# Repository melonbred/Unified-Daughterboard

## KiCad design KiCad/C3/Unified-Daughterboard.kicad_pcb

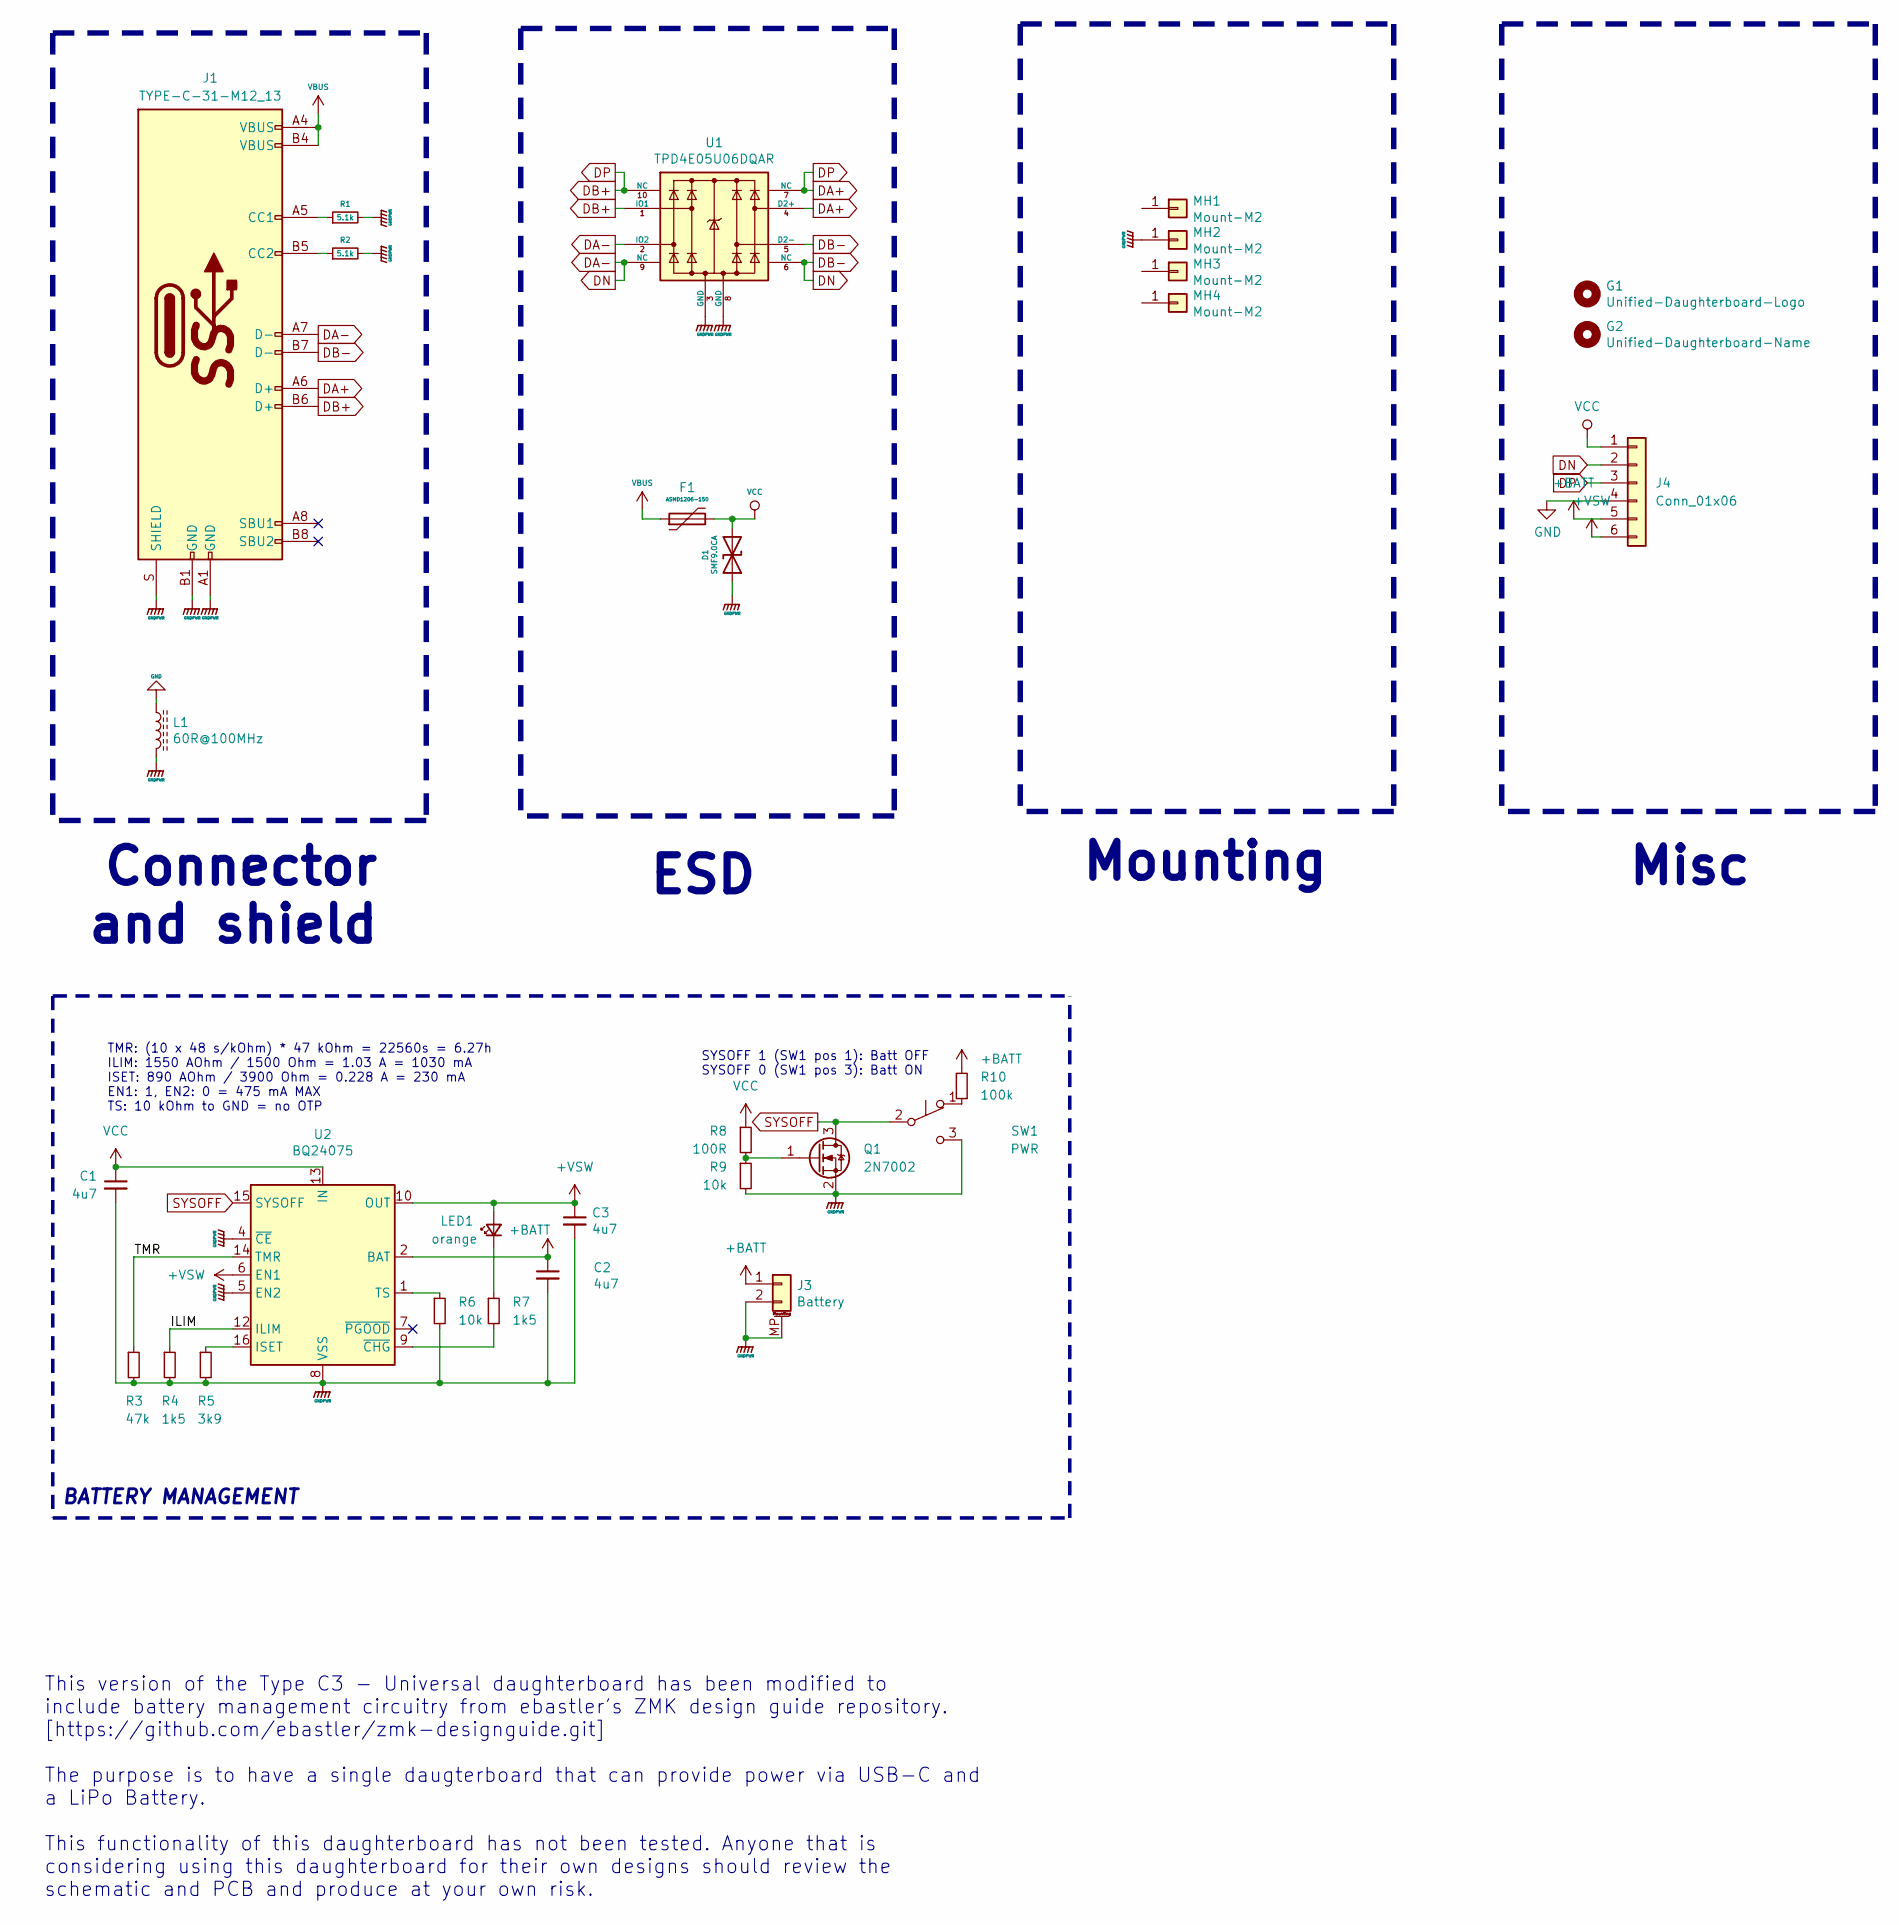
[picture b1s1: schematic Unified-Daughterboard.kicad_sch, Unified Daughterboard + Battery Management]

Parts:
C1, C2, C3: 4u7; C_0402_1005Metric
D1: SMF9.0CA; D_SOD-123_Bidirectional; Manufacturer Part No SMF9.0CA; LCSC Part No C123799
F1: ASMD1206-150; Fuse_1206_3216Metric; Manufacturer Part No ASMD1206-150; LCSC Part No C135342
G1: Unified-Daughterboard-Logo; Unified-Daughterboard-Logo.pretty
G2: Unified-Daughterboard-Name; Unified-Daughterboard-Name.pretty
J1: TYPE-C-31-M12_13; TYPE-C-31-M-12; Manufacturer Part No TYPE-C-31-M-12; LCSC Part No C165948
J3: Battery; JST_SH_SM02B-SRSS-TB_1x02-1MP_P1.00mm_Horizontal; LCSC C505023
J4: Conn_01x06; Molex_Pico-EZmate_78171-5006_1x06-1MP_P1.20mm_Vertical
L1: 60R@100MHz; L_1206_3216Metric; Manufacturer Part No MLB3216-600P4A(f); LCSC Part No C33600
LED1: orange; LED_0402_1005Metric; LCSC C917185
MH1, MH2, MH3, MH4: Mount-M2; Generic-Mounthole
Q1: 2N7002; SOT-23
R1, R2: 5.1k; R_0603
R3: 47k; R_0402_1005Metric
R4, R7: 1k5; R_0402_1005Metric
R5: 3k9; R_0402_1005Metric
R6, R9: 10k; R_0402_1005Metric
R8: 100R; R_0402_1005Metric
R10: 100k; R_0402_1005Metric
SW1: PWR; SW_MSK12C02-HB
U1: TPD4E05U06DQAR; USON-10_2.5x1.0mm_P0.5mm; Manufacturer Part No TPD4E05U06DQAR; LCSC Part No C138714
U2: BQ24075; VQFN-16-1EP_3x3mm_P0.5mm_EP1.6x1.6mm; LCSC C15464

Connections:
+BATT: C2.1, J3.1, J4.5, R10.2, U2.2 (BAT), U2.3 (BAT)
+VSW: C3.1, J4.6, LED1.2 (A), U2.6 (EN1), U2.10 (OUT), U2.11 (OUT)
/ILIM: R4.1, U2.12 (ILIM)
/TMR: R3.1, U2.14 (TMR)
DA+: J1.A6 (D+), J1.B6 (D+), J4.3, U1.1 (IO1), U1.4 (D2+), U1.7 (NC), U1.10 (NC)
DA-: J1.A7 (D-), J1.B7 (D-), J4.2, U1.2 (IO2), U1.5 (D2-), U1.6 (NC), U1.9 (NC)
GND: J4.4, L1.1
GNDPWR: C1.2, C2.2, C3.2, D1.1 (A1), J1.A1 (GND), J1.B1 (GND), J1.S (SHIELD), J3.2, J3.MP (MountPin), L1.2, MH2.1, Q1.2 (S), R1.2, R2.2, R3.2, R4.2, R5.2, R6.2, R9.2, SW1.3 (C), U1.3 (GND), U1.8 (GND), U2.4 (~CE), U2.5 (EN2), U2.8 (VSS), U2.17 (VSS)
unnamed: J1.A5 (CC1), R1.1
unnamed: J1.B5 (CC2), R2.1
unnamed: LED1.1 (K), R7.1
unnamed: Q1.1 (G), R8.2, R9.1
unnamed: R10.1, SW1.1 (A)
unnamed: R5.1, U2.16 (ISET)
unnamed: R6.1, U2.1 (TS)
unnamed: R7.2, U2.9 (~CHG)
SYSOFF: Q1.3 (D), SW1.2 (B), U2.15 (SYSOFF)
VBUS: F1.1, J1.A4 (VBUS), J1.B4 (VBUS)
VCC: C1.1, D1.2 (A2), F1.2, J4.1, R8.1, U2.13 (IN)

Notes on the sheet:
Misc
BATTERY MANAGEMENT
Mounting
This version of the Type C3 - Universal daughterboard has been modified to include battery management circuitry from ebastler's ZMK design guide repository. [https://github.com/ebastler/zmk-designguide.git] The purpose is to have a single daugterboard that can provide power via USB-C and a LiPo Bat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
TMR: (10 x 48 s/kOhm) * 47 kOhm = 22560s = 6.27h ILIM: 1550 AOhm / 1500 Ohm = 1.03 A = 1030 mA ISET: 890 AOhm / 3900 Ohm = 0.228 A = 230 mA EN1: 1, EN2: 0 = 475 mA MAX TS: 10 kOhm to GND = no OTP
ESD
Connector and shield
SYSOFF 1 (SW1 pos 1): Batt OFF SYSOFF 0 (SW1 pos 3): Batt ON

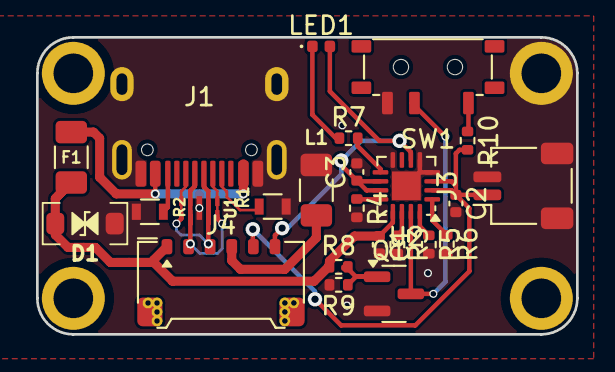
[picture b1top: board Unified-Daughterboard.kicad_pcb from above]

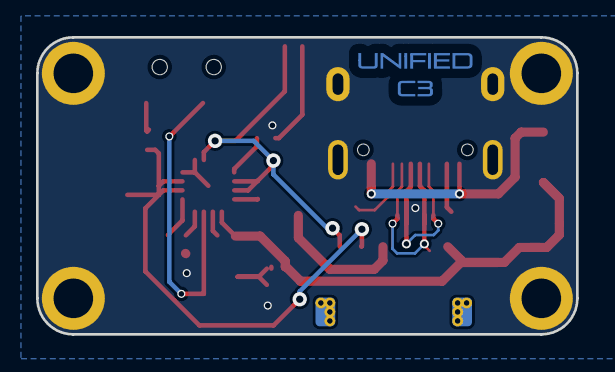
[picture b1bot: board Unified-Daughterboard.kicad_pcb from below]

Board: 2 copper layers, 30.0 x 16.5 mm, 30 parts (2 on the bottom side), 19 nets.

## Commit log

2024-10-28 Added Battery and charging management to schematic and PCB
2024-10-29 Dimensioning PCBnew
2024-11-15 STEP export
